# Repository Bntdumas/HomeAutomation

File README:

Home Automation
=============

Home automation is cool.
The thing is, it is also very expensive to buy ready-made modules. Especially if you want to automate large parts of your house.

The good news is that you can find everything you need to create your own home ayutomation system for cheap on internet,
if you don't mind putting a bit of work into it.

This is what motivates me to create my own home automatisation system.

The design goes roughly like this:
- All the house data is stored in a Qt application, running on a computer used as a server.
- Every client communicates via TCP sockets to the server, a client being an user interface or a hardware module.
- The main application hosts a TCP server that communicates both ways with the hardware modules via wifi (using the inexpensive ESP8266 modules from EspressIf)
- The TCP frames are text based, using XML for easy parsing.

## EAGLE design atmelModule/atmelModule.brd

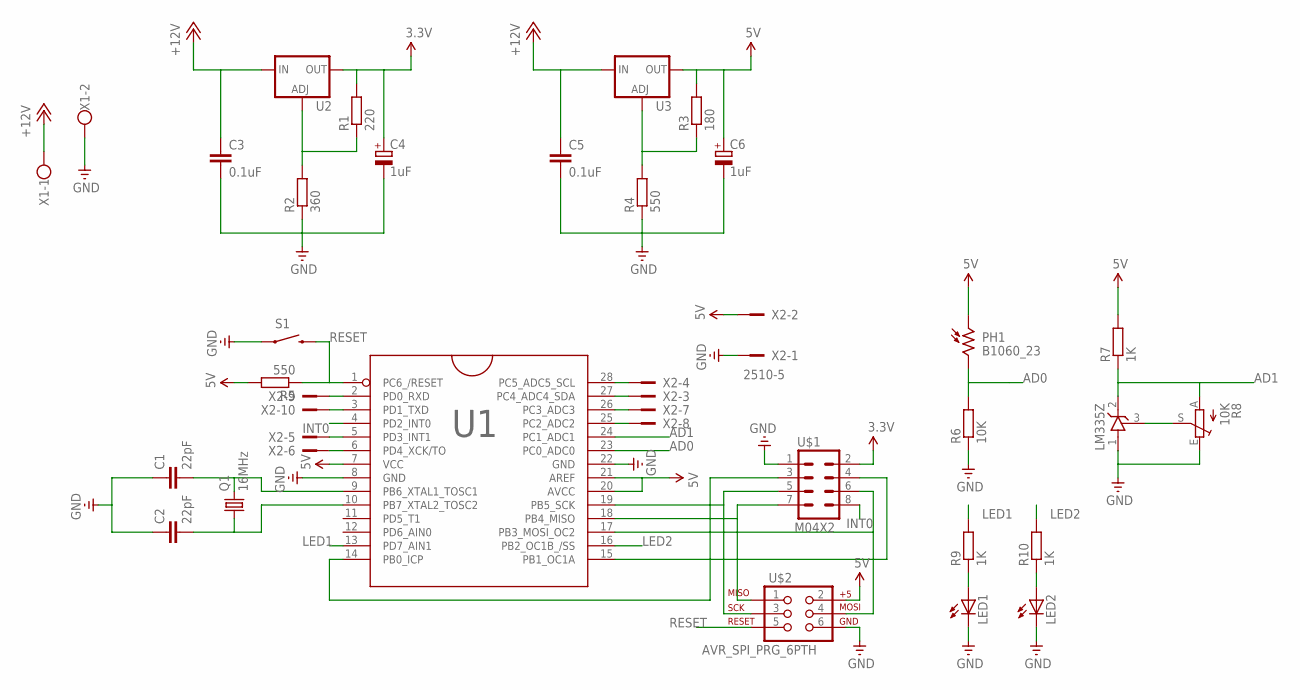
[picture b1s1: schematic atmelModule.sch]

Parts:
C1, C2: 22pF; CAP-PTH-SMALL2
C3, C5: 0.1uF; CAP-PTH-SMALL2
C4, C6: 1uF; E1,8-4
IC1: LT1009CZ; TO92
LED1, LED2: LED5MM
PH1: B1060_23; TO-8_B10
Q1: 16MHz; HC49U-V
R1: 220; 0207/7
R2: 360; 0207/7
R3: 180; 0207/7
R4, R5: 550; 0207/7
R6: 10K; 0207/7
R7, R9, R10: 1K; 0207/7
R8: 10K; RJ9W
S1: SWITCH-MOMENTARY-2PTH; TACTILE-PTH
U1: ATMEGA8_PDIP28_PDIP; DIL-28-3
U2, U3: V_REG_317SINK; TO220-ADJ
U$1: M04X2; 2X4
U$2: AVR_SPI_PRG_6PTH; 2X3
X1: W237-102
X2: 2510-5; PAK100/2500-5-10

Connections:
3.3V: C4.+, R1.2, U2.OUT, U$1.2
5V: C6.+, PH1.1, R3.2, R5.2, R7.2, U1.7 (VCC), U1.20 (AVCC), U1.21 (AREF), U3.OUT, U$2.2, X2.2
+12V: C3.1, C5.1, U2.IN, U3.IN, X1.1
AD0: PH1.2, R6.2, U1.23 (PC0_ADC0)
AD1: IC1.2 (C), R7.1, R8.A, U1.24 (PC1_ADC1)
GND: C1.1, C2.1, C3.2, C4.-, C5.2, C6.-, IC1.1 (A), LED1.K (C), LED2.K (C), R2.1, R4.1, R6.1, R8.E, S1.1, U1.8 (GND), U1.22 (GND), U$1.1, U$2.6, X1.2, X2.1
INT0: U1.4 (PD2_INT0), U$1.8
LED1: R9.2, U1.13 (PD7_AIN1)
LED2: R10.2, U1.16 (PB2_OC1B_/SS)
unnamed: C1.2, Q1.2, U1.9 (PB6_XTAL1_TOSC1)
unnamed: C2.2, Q1.1, U1.10 (PB7_XTAL2_TOSC2)
unnamed: R3.1, R4.2, U3.ADJ
unnamed: U1.14 (PB0_ICP), U$1.3
unnamed: U1.15 (PB1_OC1A), U$1.4
unnamed: U1.19 (PB5_SCK), U$1.5, U$2.3
unnamed: R1.1, R2.2, U2.ADJ
unnamed: U1.17 (PB3_MOSI_OC2), U$1.6, U$2.4
unnamed: U1.18 (PB4_MISO), U$1.7, U$2.1
unnamed: LED1.A, R9.1
unnamed: LED2.A, R10.1
unnamed: U1.3 (PD1_TXD), X2.10
unnamed: U1.5 (PD3_INT1), X2.5
unnamed: IC1.3 (R), R8.S
unnamed: U1.6 (PD4_XCK/TO), X2.6
unnamed: U1.26 (PC3_ADC3), X2.7
unnamed: U1.25 (PC2_ADC2), X2.8
unnamed: U1.2 (PD0_RXD), X2.9
unnamed: U1.27 (PC4_ADC4_SDA), X2.3
unnamed: U1.28 (PC5_ADC5_SCL), X2.4
RESET: R5.1, S1.3 (2), U1.1 (PC6_/RESET), U$2.5

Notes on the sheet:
LM335Z

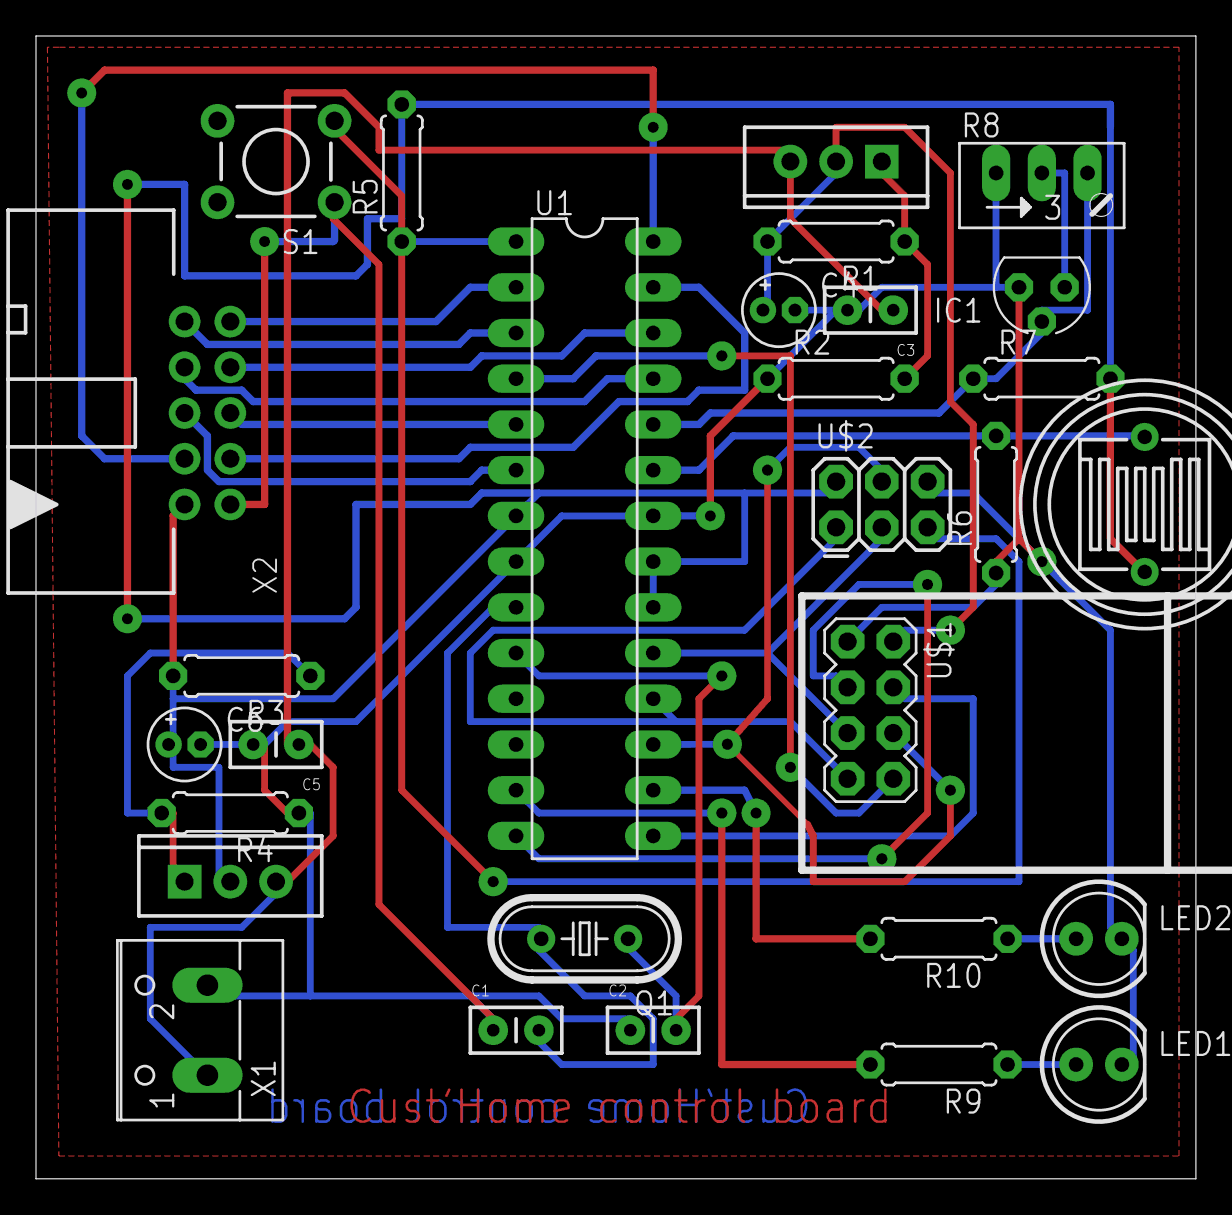
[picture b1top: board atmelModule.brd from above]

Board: 2 copper layers, 64.4 x 63.5 mm, 29 parts (0 on the bottom side), 30 nets.

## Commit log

2013-04-06 Initial commit, add images
    - Add images for the QML UI, onyl the lights so far
    - Add README
    - Add git files (gitignore and such)
2013-04-07 First implementation of the server
    Add the local files to git
2013-04-07 Update gitignore with Qt/c++ stuff
2013-10-29 Remove pictures
2013-10-29 Simplify the way plugs are handled
2013-10-29 started refactoring of the house Data
2013-11-26 Add database tools
2013-11-26 Add admin tool for the home automation system
2013-11-26 Add SQL strucutre related files
2013-11-30 Emit signals with correct enum name. Add a "success" item
2013-11-30 update gitignore
2013-11-30 update gitignore with build directories
2013-11-30 Remove \n from the read lines in a file
2013-11-30 Use correct values for database connection
    Still test values for now, localhost.
2013-11-30 Add a way to generate a short string-based uuid for the db
2013-11-30 Constructor for the database tools
2013-11-30 Add an hardware simulator
2013-11-30 Connect the admin widget to the databse admin class.
    Allow creation of the database, structure and static data from the SQL
    files
2013-11-30 Updates SQL tables definition
    - Changes in the tables structure
    - use SQL friendly comments
2013-11-30 Add actions to the admin window
2013-11-30 Add debug statements
2013-11-30 Implement deleting tables
2013-11-30 Update creation of the tables method
2013-11-30 Improve creation of the house structure.
    - Split the createHouseStructure() method to use
    addRoom(), addInput and addOutput()
    Also fixed the methods so the house structure is correcty created
2013-11-30 Remove endline character when reading file
2013-11-30 make executeSQL() more pretty
2013-11-30 Use correct parameter name
2013-11-30 Update parameters name and Doxygen
2013-11-30 fix syntax
2013-11-30 QMake subprojects
2013-11-30 remove website in readme
2013-11-30 respect lower case
2013-12-27 Add test for the HF device
2013-12-27 Add HF device class to communicate with arduino nodes
2013-12-27 prepare triggers files
2013-12-27 Add HF device bits to the home automation QMake file
2013-12-27 Prepare files for roomController
2013-12-29 Use RF24 network as a base library instead of just RF24
2014-05-13 remove old files
2014-05-13 remove old RF24 lib
2014-05-13 Add a more central way to keep the QRF24Network dependencies
2014-05-13 Remove previous files
2014-05-13 better target path for the app
2014-05-13 Move project out of "new software"
2014-05-14 Add Atmel programmer class (compile and upload sketch to Atmel board)
2014-05-14 Adapt sub projects depending on the target platform
    - Raspberry Pi: compiles the RF24 network library
    and prepare app running on it.
    - Desktop: Admin Tool, simulator
2014-05-14 Remove references to old libraries, add RF24 dependencies
2014-05-14 Convert slots to camelCase
2014-05-14 bit of documentation
2014-05-14 Integrate Atmel programmer in admin tool
2014-05-14 add atmelConfigurator page
2014-05-15 add schematics
2014-05-15 Add Eagle files
2014-05-15 add Atmel test template
2014-05-15 use the correct library
2014-05-15 add Atmel test
2014-05-15 disable sub project
2015-02-07 Start a wizard for the Atmel modules
2015-02-10 Add a wizard for the module settings
2015-03-21 fix typo
2015-03-21 add a way to force validatePage()
2015-03-21 remove double initialization of combobox
2015-03-21 use foreach()
2015-03-21 syntax fix
2015-03-21 qmake syntax fix
2015-03-21 fix qmake syntax error
2015-03-21 Implement most of the atmel module configurator
2015-03-21 display log message instead of qDebug()
2015-03-21 add a way to generate a source file from the admin window
2015-03-21 WIP implementation of the settings file generator
2015-03-21 Add example of a working pde file
2015-03-21 Different bug fixes
2015-03-21 Bug fix
2015-03-21 Improve template file
2015-03-21 Continue work on the template editor
2015-05-09 Continue implementing source file creation.
2015-05-09 Prepare project for new hardware
2015-05-09 continue reorganisation of files
2015-06-09 remove roomController, it was empty
2015-06-09 Create the home server library
    WIP of course
2015-06-09 Add an app to use the home server lib
2015-06-09 add tests for the network
2015-06-09 add missing files from pro file
2015-06-09 WIP port to CMake
2015-06-09 gitignore
2015-06-09 Decided to drop the database idea, as well as using Atmel modules.
2015-06-09 House structure is now using XML
2015-06-09 further cleanup of SQL files
2015-06-09 remove .gitattributes
2015-06-09 Further cleanup of the database ad Atmel code.
    Kinda starting from scratch now...
2015-06-10 Remove .pro
2015-06-10 Add house data structure
2015-06-10 Update admin tool to run the TCP server
2015-06-10 Update TCP server
2015-06-10 Add client simulator
2015-06-10 WIP - Add tests
2015-06-10 update CMakeLists
2015-06-10 update room xml
2015-06-10 Continue working on the tests
2015-06-10 remove file
2015-06-10 remove useless bits in homeServer
2015-06-10 fix indent
2015-06-21 WIP add unit tests for the house data structure
2015-06-21 move destructor body
2015-06-21 Add verifications for devices creation
    - Fixed enum naming (was Ouput instead of Output)
2015-06-21 Work on device creation testing
2015-06-21 name typo
2015-06-21 change description of handler
2015-06-21 fix tests
2015-06-21 fix tests.
    Unit tests are boring
2015-06-24 remove comments
2015-06-24 add C++11 flag
2015-06-24 rename tcp parser
2015-06-24 Create two TCP servers for modules and users.
    - One common class tspServer for the basics
    - One server will handle communication with the hardware modules
    - The other server will handle communication with the Qt clients
    (the users)
2015-06-24 house data Handler as a singleton
    This class will be the interface between the TCP servers and the house
    data, it needs to be singleton in order to make sure only one handler
    object can access the house at any time.
2015-06-24 Fix shared lib issues with houseData
2015-06-24 cleanup userServer
    Now needs implementation
2015-06-24 add documentation
2015-06-24 send lines to server, add '\n' automatically
2015-06-24 Improve visibility
2015-06-24 use XML for TCP frames
2015-06-24 improve simulator
2015-06-24 test if sending reset command got sent
2015-06-24 allow disabling automatic polling
2015-06-24 work on the basic server test (ping + ping back)
2015-06-24 move polling timer to protected so it can be used in inherited classes
2015-06-24 fix message queue bug
    Unit tests are boring, sure. But they help find bugs :)
2015-06-25 De-activate test
2015-06-25 reduce simulation timer so it goes faster
2015-06-25 document test
2015-06-25 Enable running whole test suite at once
2015-06-25 Add commands to module server
2015-06-25 Cleanup + indent
2015-06-25 rename method
2015-06-25 add a method to get client from it's ID
2015-06-25 add test for client pointer and rename variable (conflict)
2015-06-25 copy over LUA scripts for esp8266 modules
2015-06-25 add gpio command
2015-06-25 Add headers in sources so they are correctly displayed in creator
2015-06-25 fix name typo
2015-06-25 move devices definition to own file
    - add tests for the class
2015-06-25 Add XML lib
2015-06-25 fix wrong return
2015-06-25 use bytearray instead of strings
2015-06-25 more implementation of the module simulator
2015-06-25 prepare XML elements
2015-06-25 WIP - Add XML parsing
2015-06-25 fix tcpServer header and add a method to get module ID from IP
2015-06-25 Update tests
2015-06-25 trying to fix data sending
2015-06-27 try to improve ds18b20 handling
    - add delay
    - add test app
2015-06-27 fix XML syntax for gpio
2015-06-27 fix "compile" for lua file
2015-06-27 fix IPs
2015-06-27 remove useless file
2015-06-27 Improve shared elements
    - make a library
    - create a debug center for emitted messages from the modules
2015-06-27 Improve simulator
    - add (WIP) a way to send corrupt data from the simulator
    - Use the correct XML syntax
    - Send lots of sensor data
    - Choose if the module ID will be sent once connected to the server
2015-06-27 de-activate temperature sensor on the module
    This module is not reliable enough and makes the module hang.
2015-06-27 Update XML syntax from modules
2015-06-27 Update gpio command syntax from the server to the module
2015-06-27 automatic polling in the admin window
2015-06-27 fix debug line
2015-06-27 add string keywords for the XML parsing
2015-06-27 add a way to reset modules that didn't send their id
2015-06-27 send test gpio
2015-06-27 remove getValue
2015-06-27 add XML parsing methods
2015-06-27 forgot methods prototypes
2015-06-27 info on xml syntax
2015-06-27 update message emit
2015-06-27 remove upper case D on devices
2015-06-27 use simple quote for emits
2015-06-27 fix compile
2015-06-27 Add a gui testing tool for wifi modules
2015-06-27 Fix a bug with module reconnecting
2015-06-27 Fix server reset
    - everything needs cleanup
2015-06-27 resize columns to contents
2015-06-27 update wifi test
2015-06-27 modify gpio testing method
2015-06-28 remove files
2015-06-28 remove unecessary noize in teh debug window
2015-06-28 add some doc

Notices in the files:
parts and their libraries:
SparkFun-Capacitors: Licensing: CC v3.0 Share-Alike You are welcome to use this library for commercial purposes.
